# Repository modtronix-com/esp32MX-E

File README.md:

# esp32MX-E
This repository contains [documentation](docs), [examples](examples), [schematic, PCB files](pcb) and other information for the Modtronix esp32MX-E board. This board was initially launched on [Crowd Supply](https://www.crowdsupply.com/modtronix/esp32mx-e). It can be [ordered online](https://www.modtronix.com/esp32mx-e) from Modtronix<br>

After that, it will be available on www.modtronix.com, and most likely also for sale at www.mouser.com

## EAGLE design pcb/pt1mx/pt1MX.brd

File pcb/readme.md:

This folder contains Eagle PCB and Schematic files. They are all provided for fee, as is. We take no responsibility for any errors
or defects.

The folders contains the following.

# pt1mx
This folder contains a small prototype PCB that first onto the 2 female headers of the esp32MX-E board.

| | |
| --- | --- |
|  |  |

# pt2mx
This folder contains a larger prototype PCB that first onto the 2 female headers of the esp32MX-E board.

# pt3mx
This folder contains a baseboard for the esp32MX-E board. It is designed to be used with raised 2x7 and 2x10 male
pin headers(standard 0.1" = 2.54mm spacing). We use 14.5mm raised headers, and also have 14.5mm high PCB spacers
available. It fits into the Hammond RM2015S enclosure. The "fp_pt3mx" front panel can be used with the RM2015S
enclosure.

| | |
| --- | --- |
|  |  |

# fpan-mxe
This folder contains the frontpanel used when the esp32MX-E is used together with the pt3mx(or custom board) baseboard, and the RM2015S
enclosure. This frontpanel is a standard PCB (1 or 2 layers), with black solder mask. By default, we get them manufactured using HASL(Hot Air Solder Level) surface finish. For a bit extra, you can get it manufactured with the ENIG(Immersion Gold) surface finish, which adds a premium look.

| | |
| --- | --- |
|  |  |

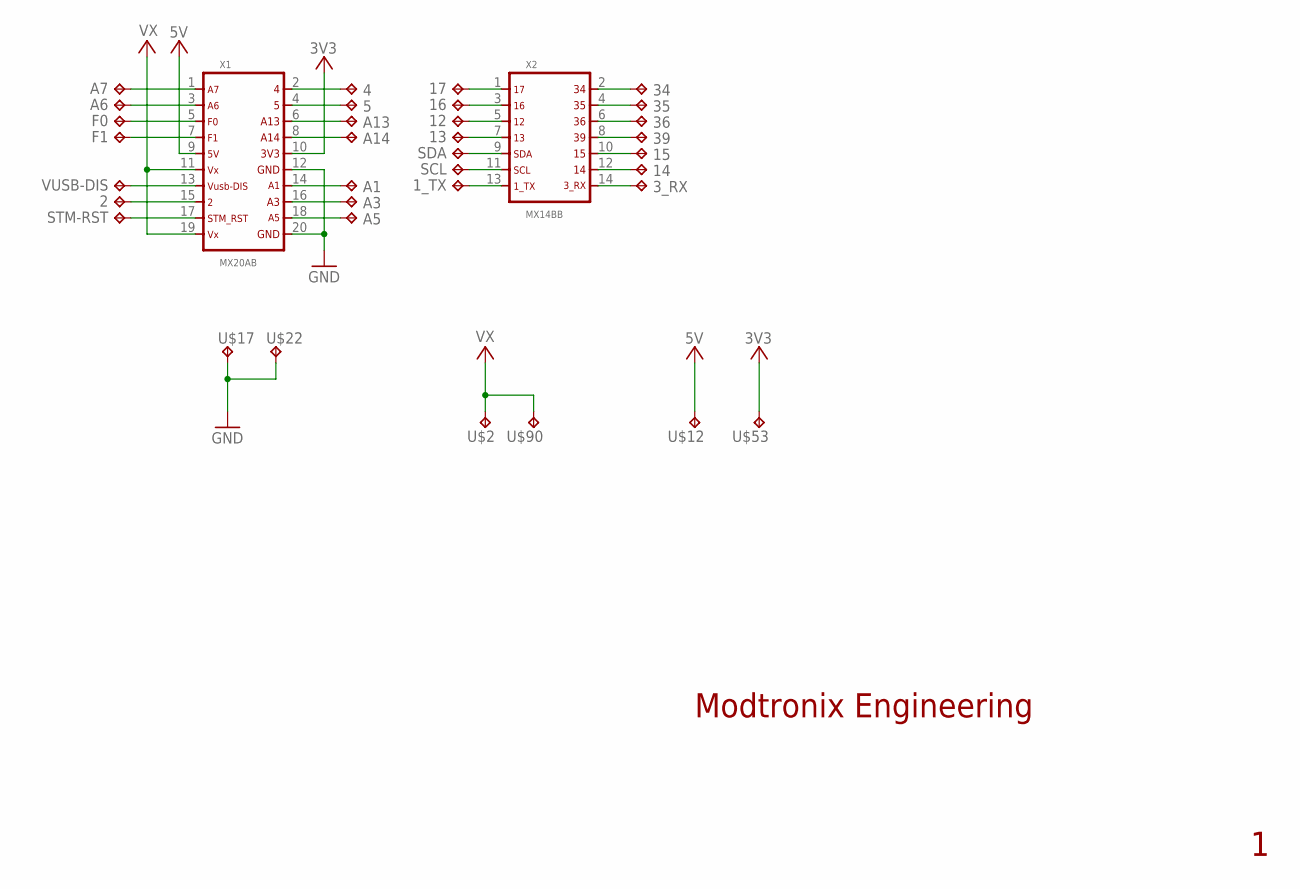
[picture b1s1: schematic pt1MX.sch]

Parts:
1_TX, 2, 3_RX, 4, 5, 12, 13, 14, 15, 16, 17, 34, 35, 36, 39: TPD10-D200; TP-10-D200
A1, A3, A5, A6, A7, A13, A14: TPD10-D200; TP-10-D200
F0, F1: TPD10-D200; TP-10-D200
SCL: TPD10-D200; TP-10-D200
SDA: TPD10-D200; TP-10-D200
STM-RST: TPD10-D200; TP-10-D200
U$2, U$12, U$17, U$22, U$53, U$90: TPD10-D200; TP-10-D200
VUSB-DIS: TPD10-D200; TP-10-D200
X1: MX20AB; MA10-2-NONUM
X2: MX14BB; MA07-2-NONUM

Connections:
1_TX: 1_TX.1, X2.13
2: 2.1, X1.15
3V3: U$53.1, X1.10
3_RX: 3_RX.1, X2.14
4: 4.1, X1.2
5: 5.1, X1.4
5V: U$12.1, X1.9
12: 12.1, X2.5
13: 13.1, X2.7
14: 14.1, X2.12
15: 15.1, X2.10
16: 16.1, X2.3
17: 17.1, X2.1
34: 34.1, X2.2
35: 35.1, X2.4
36: 36.1, X2.6
39: 39.1, X2.8
A1: A1.1, X1.14
A3: A3.1, X1.16
A5: A5.1, X1.18
A6: A6.1, X1.3
A7: A7.1, X1.1
A13: A13.1, X1.6
A14: A14.1, X1.8
F0: F0.1, X1.5
F1: F1.1, X1.7
GND: U$17.1, U$22.1, X1.12, X1.20
SCL: SCL.1, X2.11
SDA: SDA.1, X2.9
STM-RST: STM-RST.1, X1.17
VUSB-DIS: VUSB-DIS.1, X1.13
VX: U$2.1, U$90.1, X1.11, X1.19

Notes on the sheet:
Modtronix Engineering

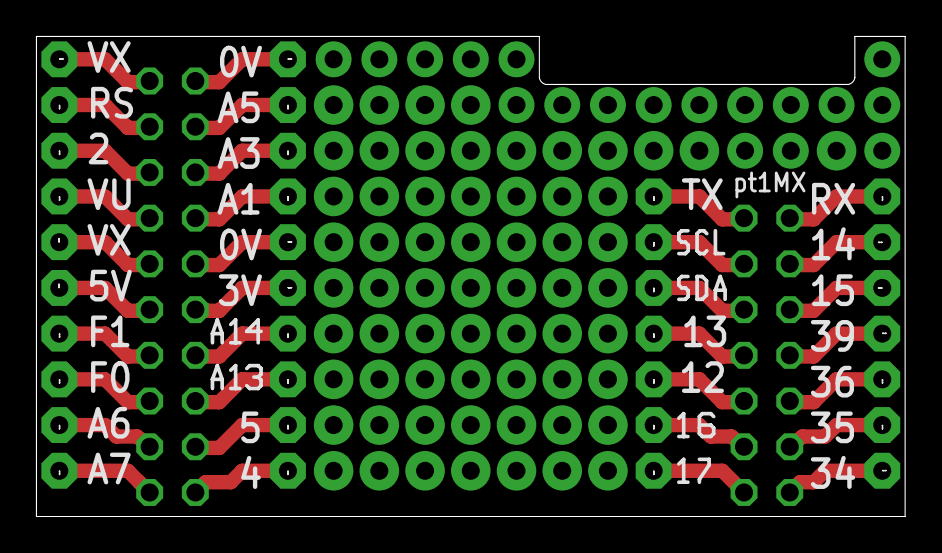
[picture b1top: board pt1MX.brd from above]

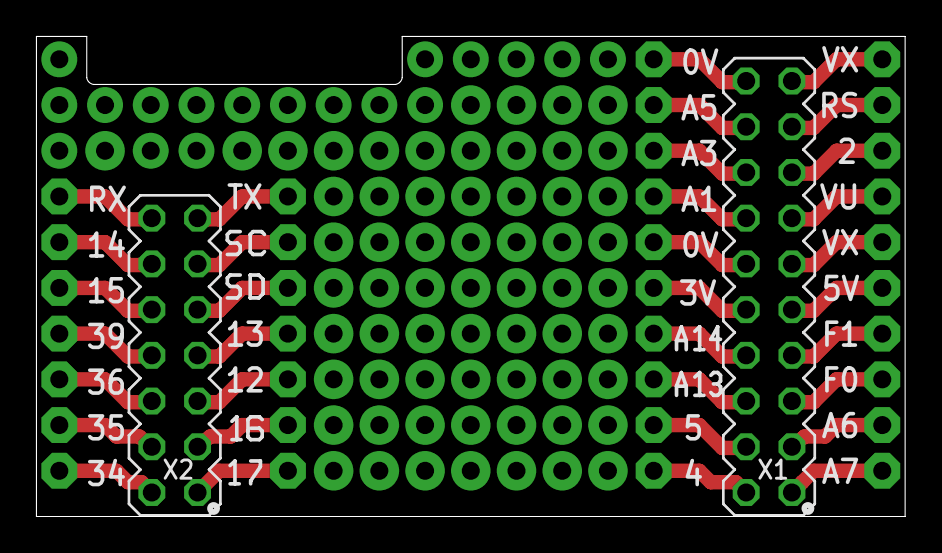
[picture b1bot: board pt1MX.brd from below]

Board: 2 copper layers, 48.3 x 26.7 mm, 67 parts (16 on the bottom side), 32 nets.

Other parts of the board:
U$1, U$4: S-56N
U$3: ESP32MX_20-14P_0H_REF
U$5: C-56N
U$6: D-56N
U$7, U$9, U$10, U$11, U$13: A-56N
U$8: L-56N
U$14: 4-56N
U$23: 3-56N
U$37: 3-56
U$39: 4-56
U$41, U$42, U$48, U$50, U$61, U$63, U$68, U$69: 1-56N
U$49, U$62: 6-56
U$51, U$54: S-56
U$52, U$64: 7-56N
U$55: D-56
U$57: C-56

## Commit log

2019-11-19 Rename Doc/readme.md to docs/readme.md
2019-11-26 Added gitignore and prototype PCBs
2019-11-26 Improved PCB images
2019-11-26 Additional images
2019-11-27 Added files
2019-11-27 Added fpan-mxe images
2019-11-27 images
2019-11-27 Update readme.md
    Added "fpan-mxe" pcb and image
2019-11-27 Added esp32MX-E Schematics
2019-11-27 Added image
2019-11-28 no message
2020-03-22 documentation
2020-03-23 Added ESP-IDF examples
2020-03-23 Added ethernet example documentation
2020-03-23 Edited Ethernet file
2020-03-23 Updated Ethernet example for ESP-IDF v4.0
2020-04-04 Arduino and Documentation
2020-04-05 Added Arduino Examples
2020-04-06 Arduino examples
2020-05-15 Added pinout image
2020-05-15 Update pinout image
2020-05-24 Added GIMP source file
2020-05-24 Added STM32 source code
